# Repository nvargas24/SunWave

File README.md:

# SunWave
Prototipo de sistema embedido "seguidor de luz" con EDUCIAA-NXP para la cátedra Técnicas Digitales 2 UTNFRH.
Se toma registro de la intensidad de luz en una cierta zona en la cual se coloca un panel solar. Dependiendo
de los datos obtenidos, por medio de un mecánismo de engranajes, se orienta el panel según la posición más eficiente.   
Con el objetivo de capturar la mayor intensidad de luz posible y de esta forma cargar una bateria de forma constante.     

# Autores  
Sr. Kyanka, Santiago  
Sr. Lopéz, Ignacio  
Sr. Vargas, Nahuel

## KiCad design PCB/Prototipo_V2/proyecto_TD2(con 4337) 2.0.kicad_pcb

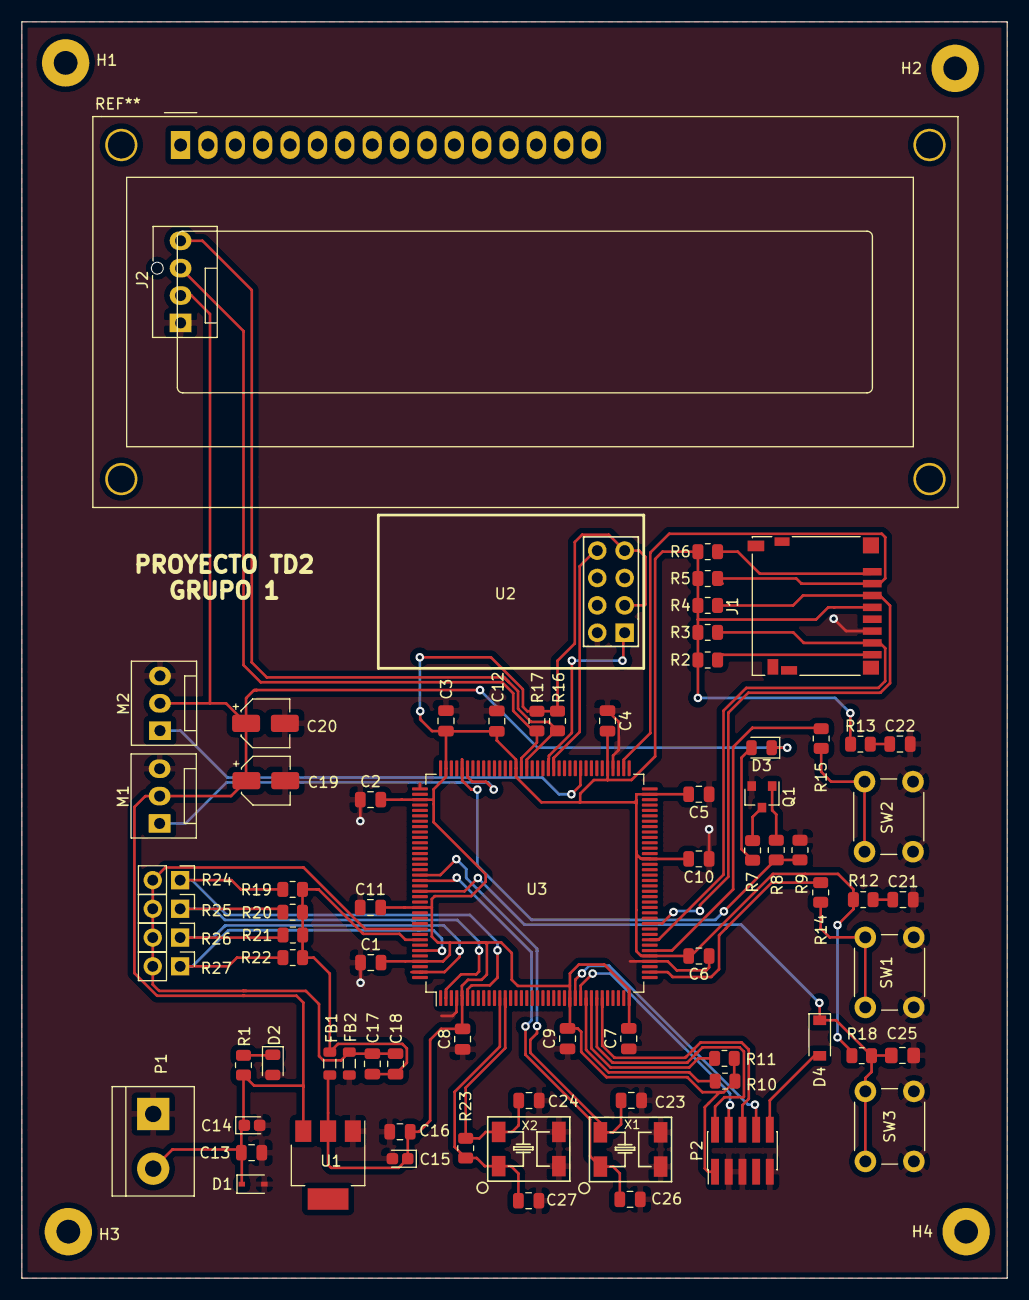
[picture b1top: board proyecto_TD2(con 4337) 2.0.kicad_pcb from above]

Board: 2 copper layers, 91.4 x 116.6 mm, 79 parts (0 on the bottom side), 43 nets.

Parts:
C1, C2, C3, C4, C5, C6, C7, C8, C9, C10, C11, C12, C13, C16, C17, C21, C22: 100nF; C_0805_2012Metric
C14, C15: 10uF; CP_EIA-1608-08_AVX-J
C18: 10nF; C_0805_2012Metric
C19, C20: 470uF; CP_Elec_4x3
C23, C24, C26, C27: 20p; C_0805_2012Metric
C25: 100nF; C_0805_2012Metric_Pad1.18x1.45mm_HandSolder
D1: ZENER; D_SOD-323
D2, D3: LED; LED_0805_2012Metric
D4: DIODE; D_SOD-123
FB1, FB2: HZ0805E601R-10; L_0805_2012Metric
H1, H2, H3, H4: MountingHole; MountingHole_2.2mm_M2_Pad
J1: Micro_SD_Card; microSD_HC_Hirose_DM3D-SF
J2: Conn_01x04; FanPinHeader_1x04_P2.54mm_Vertical
M1, M2: Motor_Servo; FanPinHeader_1x03_P2.54mm_Vertical
P1: CONN_2; TerminalBlock_bornier-2_P5.08mm
P2: Cortex - Debug; PinHeader_2x05_P1.27mm_Vertical_SMD
Q1: 2N7002; SOT-23
R1: R; R_0805_2012Metric
R2, R3, R4, R5, R6: 50k; R_0805_2012Metric
R7: 680; R_0805_2012Metric
R8, R10, R11, R12, R13, R19, R20, R21, R22: 10k; R_0805_2012Metric
R9: 330k; R_0805_2012Metric
R14, R15: 1k; R_0805_2012Metric
R16, R17: 2.2k; R_0805_2012Metric
R18: 100k; R_0805_2012Metric
R23: 10M; R_0805_2012Metric
R24, R25, R26, R27: LDR03; PinHeader_1x02_P2.54mm_Vertical
SW1, SW2, SW3: SW_PUSH; SW_PUSH_6mm
U1: NCP1117ST33T3G; SOT-223
U2: ESP-01v090; ESP-01
U3: LPC4337JBD144; LQFP-144_20x20mm_P0.5mm
X1, X2: CRYSTAL_4Pin_Mini_GND; 4SOJ

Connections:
+3.3V: C1.2, C2.2, C3.2, C4.2, C5.2, C6.2, C7.2, C8.2, C9.2, C10.2, C11.2, C12.2, C15.1, C16.1, FB1.1, J1.4, P2.1, R2.1, R3.1, R4.1, R5.1, R6.1, R10.1, R11.1, R12.2, R13.2, R16.1, R17.1, R18.1, U1.2, U2.3, U2.7, U3.5, U3.25, U3.36, U3.41, U3.59, U3.71, U3.77, U3.94, U3.107, U3.111, U3.131, U3.141
+5V: C13.1, C14.1, C19.1, C20.1, D1.2, D3.1, J2.2, M1.2, M2.2, P1.2, R1.1, U1.3
/ADC0_0: R19.2, R24.1, U3.6
/ADC0_1: R20.2, R25.1, U3.2
/ADC0_2: R21.2, R26.1, U3.143
/ADC0_3: R22.2, R27.1, U3.139
/I2C_SCL: J2.4, R16.2, U3.92
/I2C_SDA: J2.3, R17.2, U3.93
/LED1: R8.2, R9.2, U3.104
/PULS_0: R14.2, U3.38
/PULS_1: R15.2, U3.42
/PWM_S.HORIZONTAL: M2.1, U3.82
/PWM_S.VERTICAL: M1.1, U3.103
/RESET: D4.2, P2.10
/RS232_RXD: U2.1, U3.88
/RS232_TXD: U2.8, U3.87
/RTCX1: C23.1, U3.125, X1.4
/RTCX2: C26.1, U3.126, X1.1
/SPI_CS: J1.2, R5.2, U3.74
/SPI_MISO: J1.7, R3.2, U3.44
/SPI_MOSI: J1.3, R4.2, U3.47
/TCK: P2.4, U3.27
/TDI: P2.8, U3.26
/TDO: P2.6, U3.31
/TMS: P2.2, U3.30
/XTAL1: C27.1, R23.2, U3.12, X2.1
/XTAL2: C24.1, R23.1, U3.13, X2.4
/nRESET: C25.1, D4.1, R18.2, SW3.2, U3.128
/nTRST: R11.2, U3.29
GND: C1.1, C2.1, C3.1, C4.1, C5.1, C6.1, C7.1, C8.1, C9.1, C10.1, C11.1, C12.1, C13.2, C14.2, C15.2, C16.2, C19.2, C20.2, C21.2, C22.2, C23.2, C24.2, C25.2, C26.2, C27.2, D1.1, D2.2, FB2.1, J1.6, J2.1, M1.3, M2.3, P1.1, P2.3, P2.5, P2.9, Q1.2, R9.1, SW1.2, SW2.2, SW3.1, U1.1, U2.2, U3.4, U3.40, U3.76, U3.109, X1.2, X1.3, X2.2, X2.3
GNDA: C17.2, C18.2, FB2.2, R24.2, R25.2, R26.2, R27.2, U3.135
unnamed: C21.1, R12.1
unnamed: C22.1, R13.1
unnamed: D2.1, R1.2
unnamed: D3.2, R7.1
unnamed: J1.1, R6.2
unnamed: J1.8, R2.2
unnamed: Q1.1, R8.1
unnamed: Q1.3, R7.2
unnamed: R10.2, U3.28
unnamed: R14.1, SW1.1
unnamed: R15.1, SW2.1
VDDA: C17.1, C18.1, FB1.2, R19.1, R20.1, R21.1, R22.1, U3.137

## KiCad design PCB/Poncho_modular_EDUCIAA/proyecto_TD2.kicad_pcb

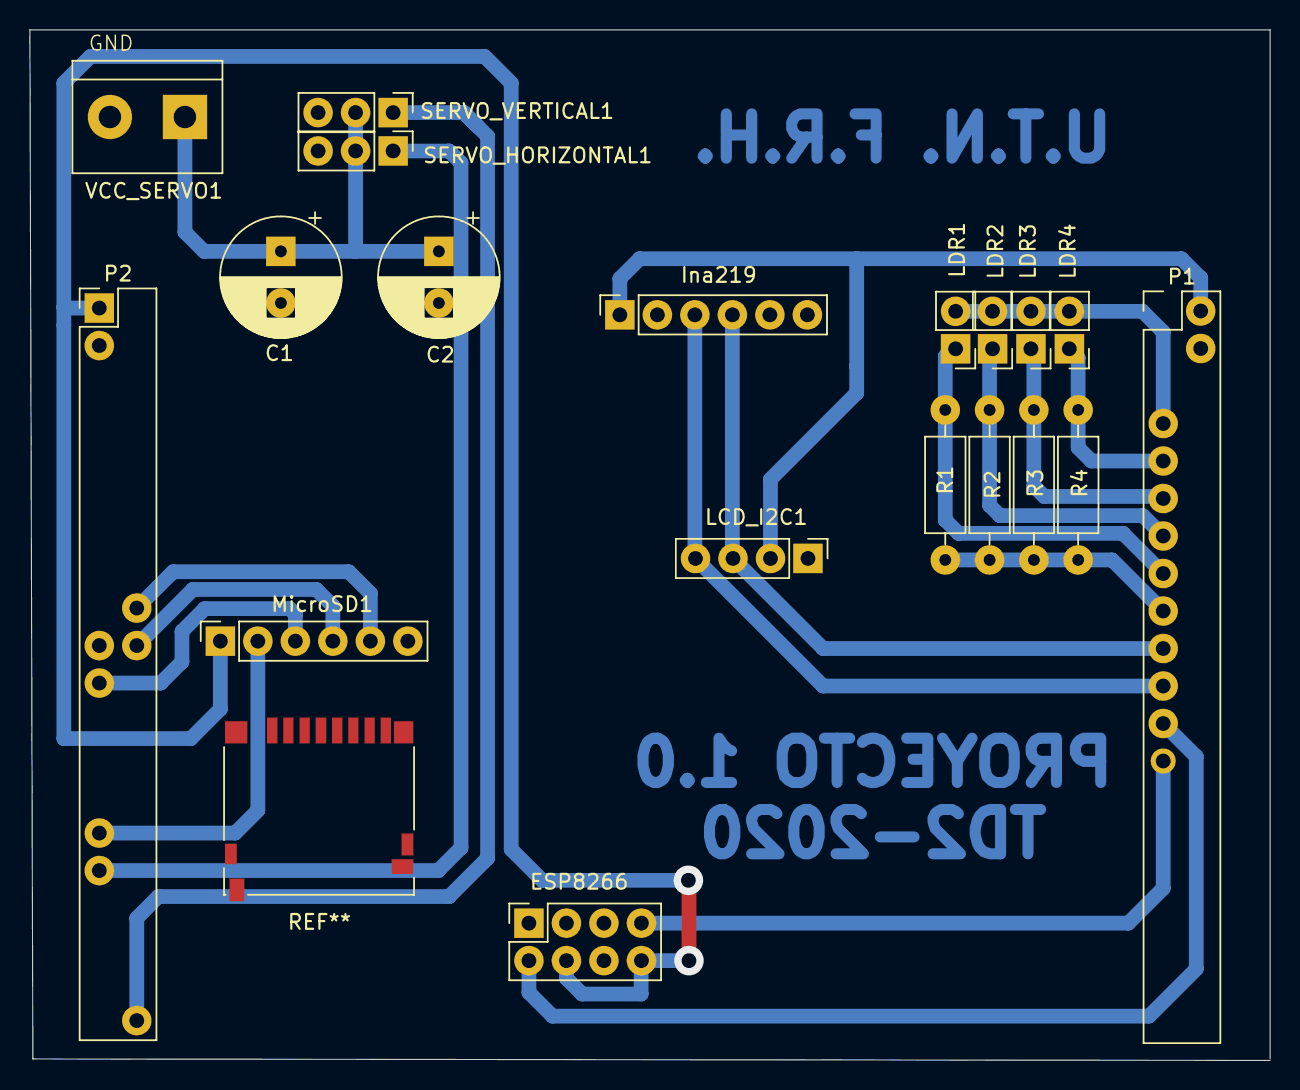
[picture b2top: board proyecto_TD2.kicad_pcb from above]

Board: 2 copper layers, 84.0 x 69.8 mm, 19 parts (0 on the bottom side), 20 nets.

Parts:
C1, C2: 470u; CP_Radial_D8.0mm_P3.50mm
ESP8266: Conn_02x04_Top_Bottom; PinSocket_2x04_P2.54mm_Vertical
Ina219: Ina219; PinSocket_1x06_P2.54mm_Vertical
LCD_I2C1: Conn_01x04; PinHeader_1x04_P2.54mm_Vertical
LDR1, LDR2, LDR3, LDR4: LDR03; PinHeader_1x02_P2.54mm_Vertical
MicroSD1: Conn_01x06; PinSocket_1x06_P2.54mm_Vertical
P1, P2: CONN_20X2; PinHeader_2x20_P2.54mm_Vertical
R1, R2, R3, R4: 10k; R_Axial_DIN0207_L6.3mm_D2.5mm_P10.16mm_Horizontal
SERVO_HORIZONTAL1: Motor_Servo; PinHeader_1x03_P2.54mm_Vertical
SERVO_VERTICAL1: Motor_Servo; PinHeader_1x03_P2.54mm_Vertical
VCC_SERVO1: Screw_Terminal_01x02; TerminalBlock_bornier-2_P5.08mm

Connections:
+3.3V: ESP8266.4, ESP8266.8, MicroSD1.1, P2.1
+3.3VADC: P1.17, R1.1, R2.1, R3.1, R4.1
+5V: Ina219.1, LCD_I2C1.2, P1.2
+VDC: C1.1, C2.1, SERVO_HORIZONTAL1.2, SERVO_VERTICAL1.2, VCC_SERVO1.1
/CH1: LDR2.1, P1.13, R2.2
/CH2: LDR3.1, P1.11, R3.2
/CH3: LDR4.1, P1.9, R4.2
/CS_SD: MicroSD1.2, P2.29
/DAC: LDR1.1, P1.15, R1.2
/ESP_RX: ESP8266.7, P1.25
/ESP_TX: ESP8266.2, P1.23
/I2C_SCL: Ina219.3, LCD_I2C1.4, P1.21
/I2C_SDA: Ina219.4, LCD_I2C1.3, P1.19
/PWM_SERVO_H: P2.31, SERVO_HORIZONTAL1.1
/PWM_SERVO_V: P2.40, SERVO_VERTICAL1.1
/SPI_MISO: MicroSD1.5, P2.18
/SPI_MOSI: MicroSD1.3, P2.21
/SPI_SCK: MicroSD1.4, P2.20
GND: C1.2, C2.2, ESP8266.1, Ina219.2, LCD_I2C1.1, MicroSD1.6, P1.4, P2.3, P2.19, SERVO_HORIZONTAL1.3, SERVO_VERTICAL1.3, VCC_SERVO1.2
GNDA: LDR1.2, LDR2.2, LDR3.2, LDR4.2, P1.7

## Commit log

2023-09-07 firmware de educiaa
2023-09-07 resultados
